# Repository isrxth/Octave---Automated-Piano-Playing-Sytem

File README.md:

###### 🎹 Project Octave

###### 

###### By Team WeBeSyncing

###### 

###### Project Octave is a high-speed, polyphonic, CNC-style robotic piano playing system. Utilizing a multi-microcontroller architecture, ESP-NOW wireless synchronization, and a custom lookahead kinematic engine, Octave translates standard .mid files into precise physical movements, playing an acoustic piano with superhuman speed and accuracy.

https://github.com/user-attachments/assets/f8b78fd2-65e9-428f-8b61-9593326f1c79

###### ✨ Key Features

###### 

###### &#x20;   Polyphonic "Cluster" Engine: Groups simultaneous MIDI notes and calculates a "Center of Gravity" offset, allowing a rigid solenoid block to perfectly strike multiple keys at once.

###### 

###### &#x20;   Anti-Flood Staggering: Automatically spaces out simultaneous polyphonic WebSocket commands by 15ms to prevent Arduino Uno serial buffer overflow and dropped notes.

###### 

###### &#x20;   Lookahead Background Pre-Positioning: The Web UI calculates future moves and silently drives the stepper carriages into position during the natural musical rests, eliminating mechanical latency.

###### 

###### &#x20;   Strict Hardware Interlock: A closed-loop feedback system using ESP-NOW guarantees that solenoids will never fire while the carriage is in transit, completely protecting the 3D-printed mounts from lateral shear forces.

###### 

###### &#x20;   Dynamic Velocity Control: Maps MIDI velocity data to hardware PWM duty cycles, allowing for expressive, dynamic play (Soft vs. Hard strikes), or strict binary toggling.

###### 

###### &#x20;   Asynchronous Web UI: A beautiful, dark-mode TailwindCSS web interface hosted directly on the ESP32. Features live BPM scaling, dynamic clearance tuning, and an interactive virtual keyboard.

###### 

###### &#x20;   Over-The-Air (OTA) Updates: Fully integrated ElegantOTA allows for flashing firmware to the embedded microcontrollers via Wi-Fi without dismantling the piano hardware.

###### 

###### 🧠 System Architecture

###### 

###### Octave uses a distributed computing model to ensure non-blocking, real-time performance.

###### 1\. The Master Node (ESP32)

###### 

###### &#x20;   Hosts the Web UI (test.html) via ESPAsyncWebServer.

###### 

###### &#x20;   Receives WebSocket commands from the user's browser.

###### 

###### &#x20;   Directly drives the Black Key Solenoids (S1 - S5) via hardware PWM.

###### 

###### &#x20;   Broadcasts MOVE commands to the Stepper Node over ESP-NOW.

###### 

###### &#x20;   Sends Serial commands to the Arduino Uno.

###### 

###### 2\. The Stepper Node (ESP32)

###### 

###### &#x20;   Listens for ESP-NOW packets and drives two NEMA 17 stepper motors using AccelStepper.

###### 

###### &#x20;   Motor 1 (White Carriage): Uses sliding-window nearest-neighbor logic to traverse the white keys.

###### 

###### &#x20;   Motor 2 (Black Carriage): Uses inverted, octave-locked kinematics to perfectly align with the irregular 2-and-3 black key clusters.

###### 

###### &#x20;   Reads physical limit switches and transmits AT\_TARGET packets back to the Master to unlock the software thread.

###### 

###### 3\. The Strike Node (Arduino Uno)

###### 

###### &#x20;   Receives ultra-fast Serial packets from the Master ESP32 via a logic level shifter.

###### 

###### &#x20;   Manages a non-blocking 40ms ballistic state machine for the 7 White Key Solenoids.

###### 

###### &#x20;   Utilizes a custom 1kHz Software PWM engine for digital pins to maintain a 23% low-current hold state, preventing coil burnout.

###### 

###### 🛠️ Hardware Requirements

###### 

###### &#x20;   2x ESP32 Development Boards

###### 

###### &#x20;   1x Arduino Uno R3

###### 

###### &#x20;   2x NEMA 17 Stepper Motors (w/ TMC2209 or A4988 Drivers)

###### 

###### &#x20;   12x 15N Push-Pull Solenoids

###### 

###### &#x20;   3D-Printed Carriages \& Solenoid Mounts

###### 

###### &#x20;   12V / 24V Power Supplies \& Logic Level Converters (HW-209)

###### 

###### 🛜 Changing the Wi-Fi Network Name (SSID)

###### 

###### By default, the Master ESP32 creates a hotspot named POCOF3. Because the Master and Stepper nodes must communicate, their network credentials must match perfectly.

###### 

###### &#x20;   Open solenoid\_esp.cpp (Master) and modify:

###### &#x20;   C++

###### 

###### &#x20;   const char\* hotspotSSID     = "Project\_Octave"; // Your new name

###### &#x20;   const char\* hotspotPassword = "00000000";       // Your new password

###### 

###### &#x20;   Open stepper\_esp.cpp (Stepper) and ensure lines 8 \& 9 match exactly.

###### 

###### &#x20;   Re-flash both ESP32s.

###### 

###### 🚀 Installation \& Setup

###### 1\. Flash the Firmware

###### 

###### &#x20;   Open the project in PlatformIO or the Arduino IDE.

###### 

###### &#x20;   Install the required libraries: ESPAsyncWebServer, AsyncTCP, AccelStepper, ElegantOTA.

###### 

###### &#x20;   Flash solenoid\_esp.cpp and stepper\_esp.cpp to your respective ESP32s.

###### 

###### &#x20;   Flash solenoid\_uno.ino to your Arduino Uno.

###### 

###### 2\. Connect to the UI

###### 

###### &#x20;   Power on the Master ESP32.

###### 

###### &#x20;   Connect your computer/tablet to the Octave Wi-Fi hotspot.

###### 

###### &#x20;   Open your web browser and navigate to the ESP32's IP address (default: http://192.168.4.1).

###### 

###### &#x20;   Enter the IP into the Master Control UI and click CONNECT WS.

###### 

###### 🎹 Polyphony Limits \& Hardware Constraints

###### 

###### While the software fully supports polyphonic MIDI playback, it is bound by the physical laws of the rigid 3D-printed solenoid blocks.

###### 

###### &#x20;   The Span Limit: The system can play multiple notes at the exact same time, but they must physically fit under the 7-solenoid white carriage or the 5-solenoid black carriage. \* The Outlier Drop: If a MIDI file demands a C3 and a C5 simultaneously, the carriage cannot stretch. The software's Cluster Engine will calculate a "Center of Gravity" to cover the densest cluster of notes and safely ignore the unreachable outliers to prevent the motors from destroying the mounts.

###### 

###### 🎯 Usage \& Tuning

###### 

###### Once connected to the UI, you can calibrate Octave to match your specific physical build:

###### 

###### &#x20;   White Home / Black Home: Adjust these steps to perfectly align the 3D-printed carriages over the physical C3 octave. (Note: Black Home uses inverted kinematics, so its home step is a high value like 2400).

###### 

###### &#x20;   Clearance (ms): The mechanical time allowed for the 15N solenoid springs to pull the metal slugs out of the keybed before the stepper motors are allowed to move. Lower this value for faster songs, but ensure the slugs clear the keys to avoid lateral dragging.

###### 

###### &#x20;   Target BPM: The live tempo scaler. You can speed up or slow down a loaded MIDI file in real-time.

###### 

###### 📝 License \& Credits

## Schematics & PCB

###### 

###### Developed by Team WeBeSyncing.

###### Built for the intersection of Embedded Systems, Mechanical Engineering, and Music.

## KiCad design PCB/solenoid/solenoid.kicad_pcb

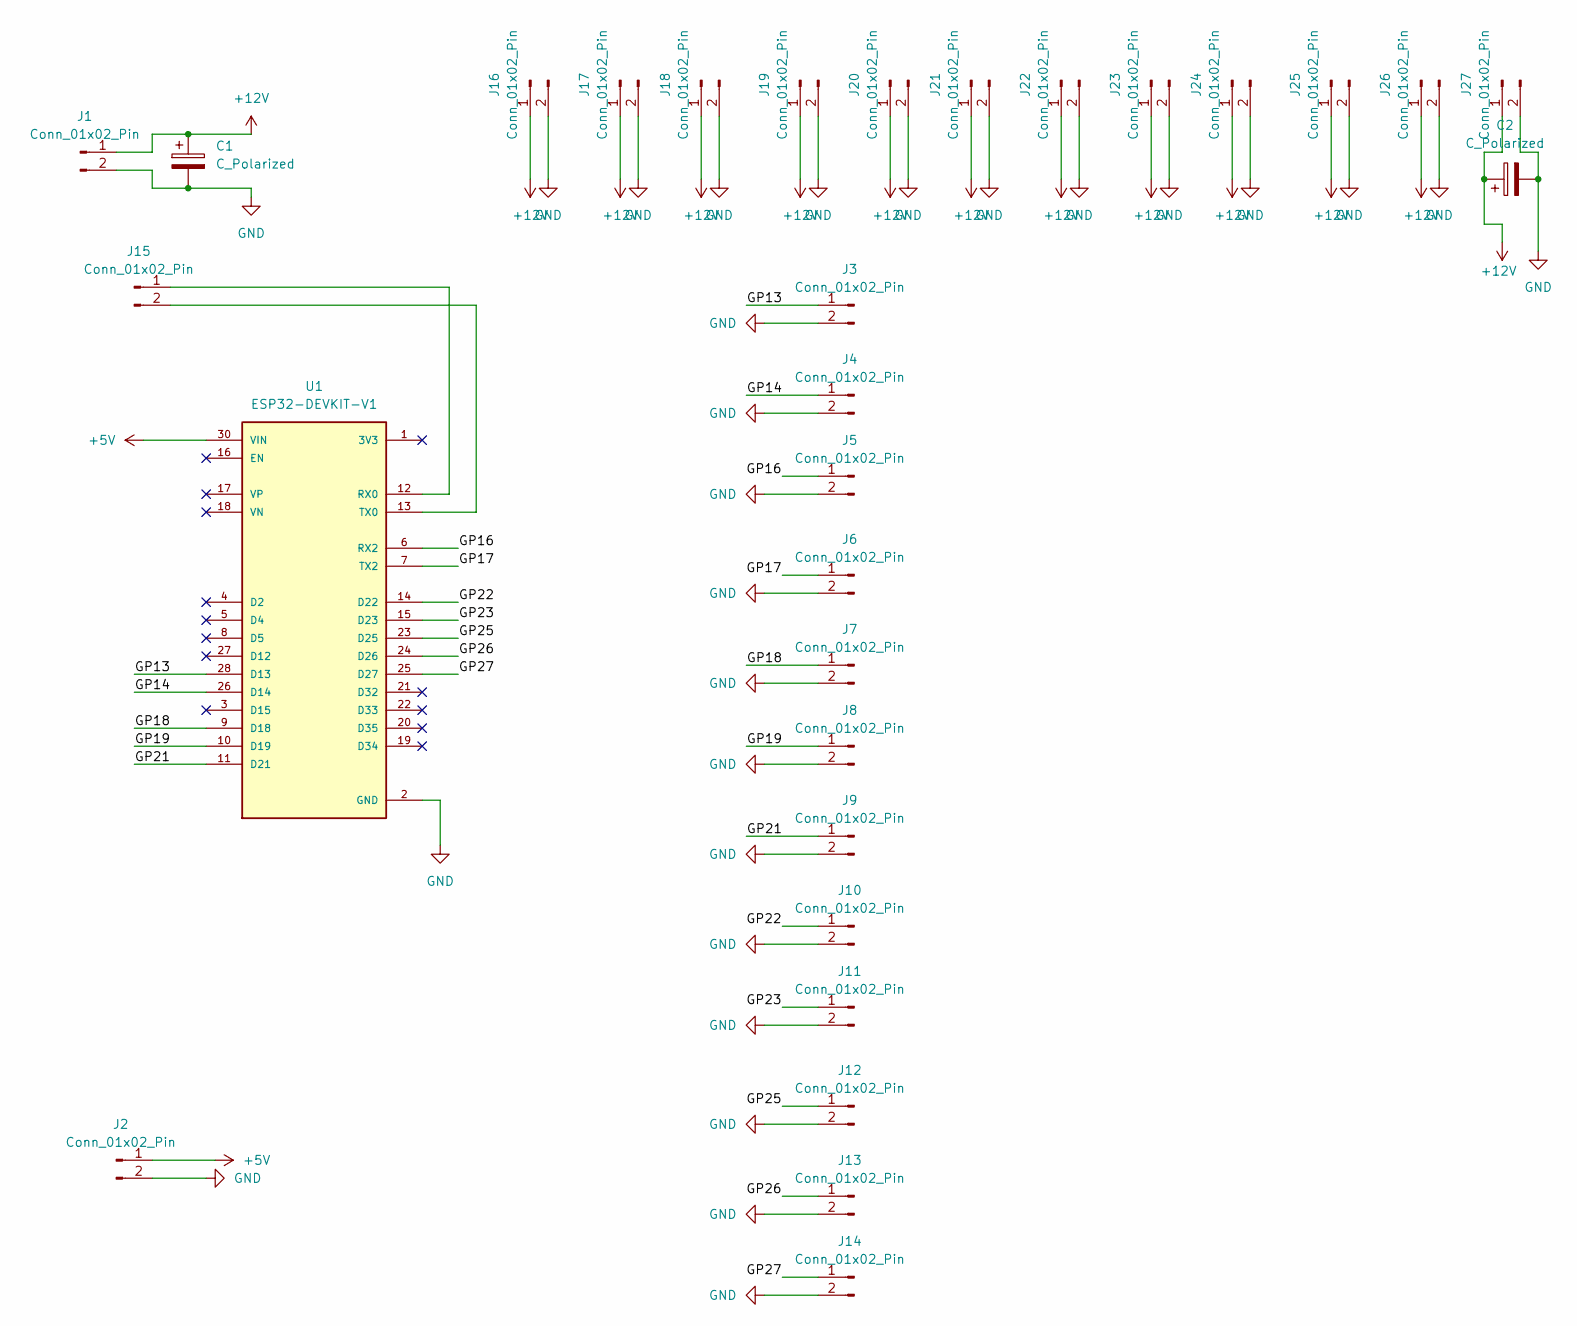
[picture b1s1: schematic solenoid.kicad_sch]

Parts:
C1, C2: C_Polarized; CP_Radial_D10.0mm_P5.00mm
J1, J2, J16, J17, J18, J19, J20, J21, J22, J23, J24, J25, J26, J27: Conn_01x02_Pin; TerminalBlock_Phoenix_PT-1,5-2-3.5-H_1x02_P3.50mm_Horizontal
J3, J4, J5, J6, J7, J8, J9, J10, J11, J12, J13, J14, J15: Conn_01x02_Pin; PinHeader_1x02_P2.54mm_Vertical
U1: ESP32-DEVKIT-V1; MODULE_ESP32_DEVKIT_V1; PARTREV N/A

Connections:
+5V: J2.1, U1.30 (VIN)
+12V: C1.1, C2.1, J1.1, J16.1, J17.1, J18.1, J19.1, J20.1, J21.1, J22.1, J23.1, J24.1, J25.1, J26.1, J27.1
/GP13: J3.1, U1.28 (D13)
/GP14: J4.1, U1.26 (D14)
/GP16: J5.1, U1.6 (RX2)
/GP17: J6.1, U1.7 (TX2)
/GP18: J7.1, U1.9 (D18)
/GP19: J8.1, U1.10 (D19)
/GP21: J9.1, U1.11 (D21)
/GP22: J10.1, U1.14 (D22)
/GP23: J11.1, U1.15 (D23)
/GP25: J12.1, U1.23 (D25)
/GP26: J13.1, U1.24 (D26)
/GP27: J14.1, U1.25 (D27)
GND: C1.2, C2.2, J1.2, J2.2, J3.2, J4.2, J5.2, J6.2, J7.2, J8.2, J9.2, J10.2, J11.2, J12.2, J13.2, J14.2, J16.2, J17.2, J18.2, J19.2, J20.2, J21.2, J22.2, J23.2, J24.2, J25.2, J26.2, J27.2, U1.2 (GND), U1.29 (GND)
unnamed: J15.1, U1.12 (RX0)
unnamed: J15.2, U1.13 (TX0)

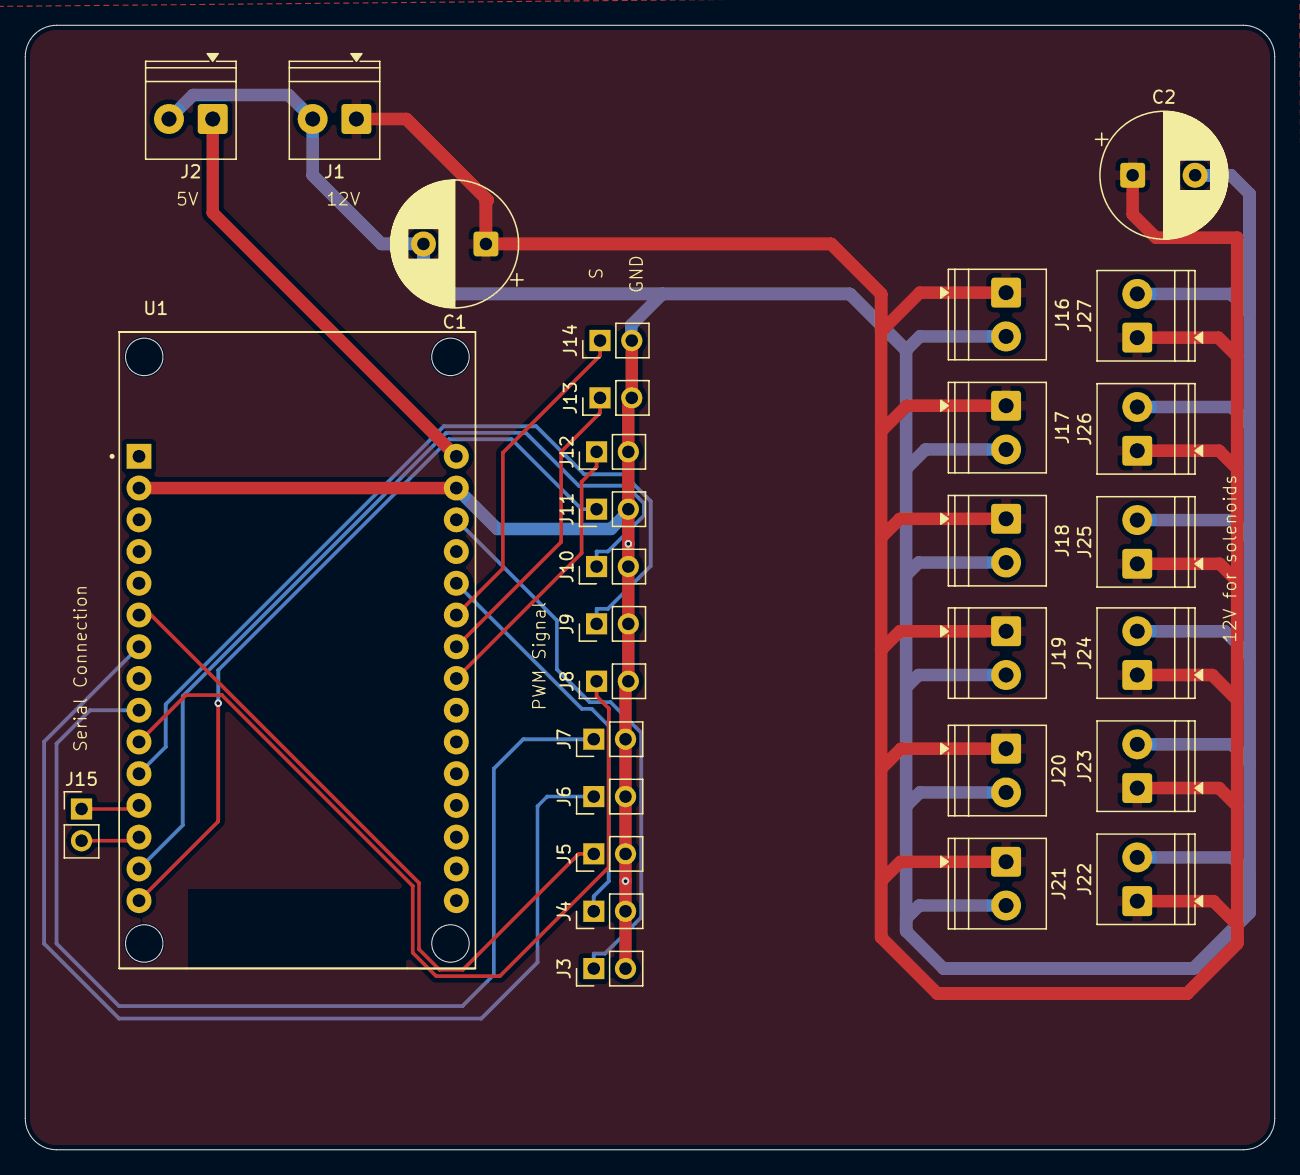
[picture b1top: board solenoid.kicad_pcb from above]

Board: 2 copper layers, 100.0 x 90.0 mm, 30 parts (0 on the bottom side), 17 nets.

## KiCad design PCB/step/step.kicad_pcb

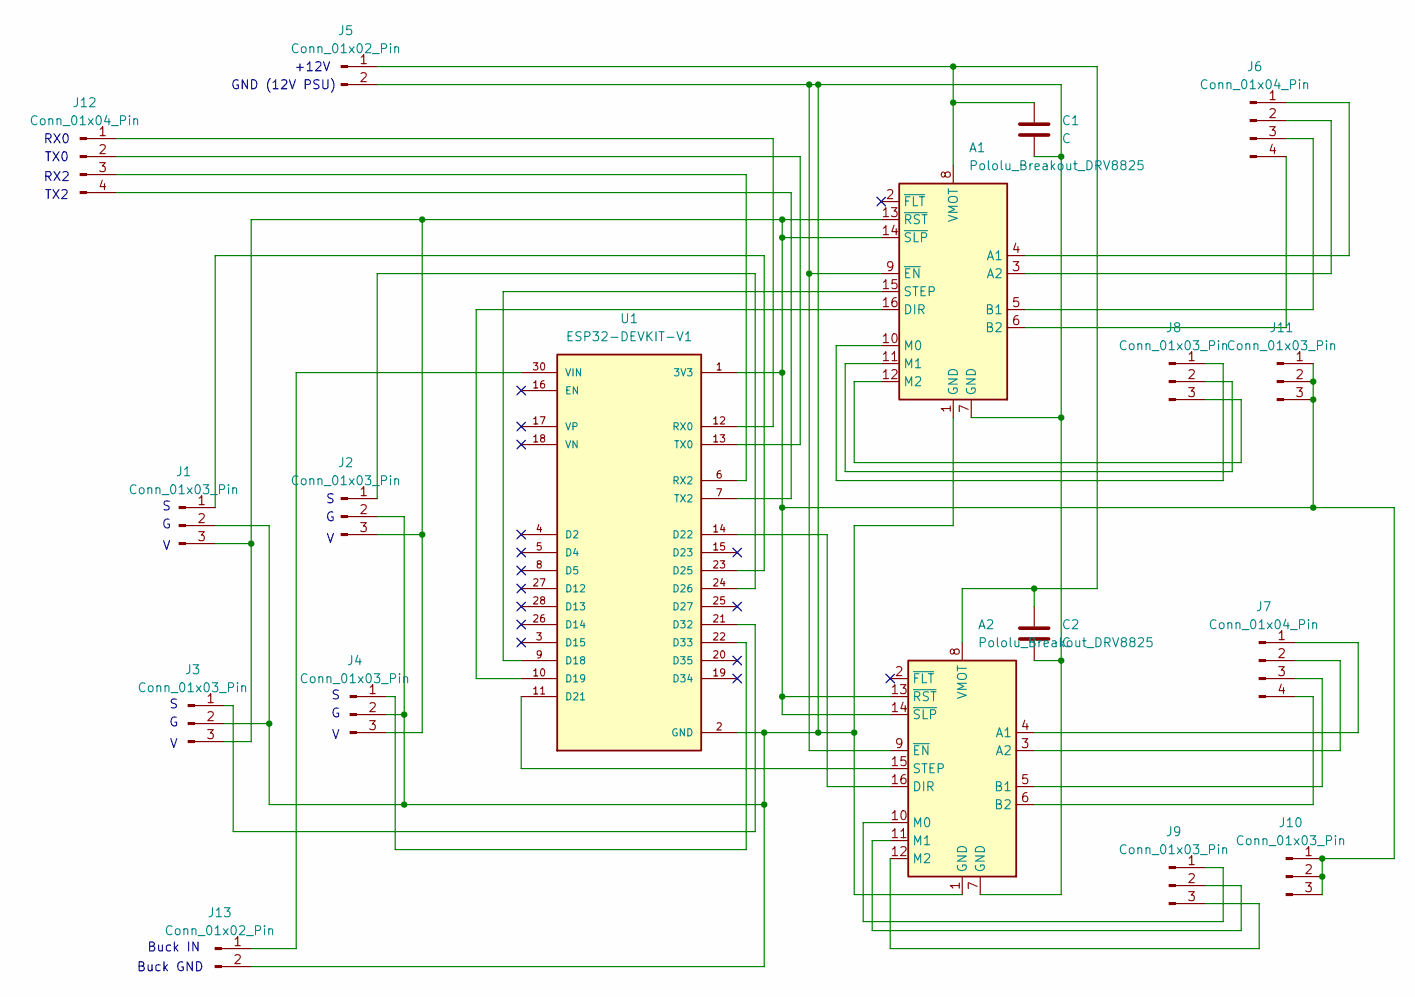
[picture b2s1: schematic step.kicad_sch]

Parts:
A1, A2: Pololu_Breakout_DRV8825; Pololu_Breakout-16_15.2x20.3mm
C1, C2: C; CP_Radial_D8.0mm_P3.50mm
J1, J2, J3, J4, J8, J9, J10, J11: Conn_01x03_Pin; PinHeader_1x03_P2.54mm_Vertical
J5, J13: Conn_01x02_Pin; TerminalBlock_Phoenix_PT-1,5-2-3.5-H_1x02_P3.50mm_Horizontal
J6, J7, J12: Conn_01x04_Pin; PinHeader_1x04_P2.54mm_Vertical
U1: ESP32-DEVKIT-V1; MODULE_ESP32_DEVKIT_V1; PARTREV N/A

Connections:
GND: A1.1 (GND), A1.7 (GND), A1.9 (~EN), A2.1 (GND), A2.7 (GND), A2.9 (~EN), C1.2, C2.2, J1.2, J2.2, J3.2, J4.2, J5.2, J13.2, U1.2 (GND), U1.29 (GND)
unnamed: A1.4 (A1), J6.1
unnamed: A1.3 (A2), J6.2
unnamed: A1.5 (B1), J6.3
unnamed: A1.6 (B2), J6.4
unnamed: A1.16 (DIR), U1.10 (D19)
unnamed: A1.10 (M0), J8.1
unnamed: A1.11 (M1), J8.2
unnamed: A1.12 (M2), J8.3
unnamed: A1.15 (STEP), U1.9 (D18)
unnamed: A1.8 (VMOT), A2.8 (VMOT), C1.1, C2.1, J5.1
unnamed: A1.13 (~RST), A1.14 (~SLP), A2.13 (~RST), A2.14 (~SLP), J1.3, J2.3, J3.3, J4.3, J10.1, J10.2, J10.3, J11.1, J11.2, J11.3, U1.1 (3V3)
unnamed: A2.4 (A1), J7.1
unnamed: A2.3 (A2), J7.2
unnamed: A2.5 (B1), J7.3
unnamed: A2.6 (B2), J7.4
unnamed: A2.16 (DIR), U1.14 (D22)
unnamed: A2.10 (M0), J9.1
unnamed: A2.11 (M1), J9.2
unnamed: A2.12 (M2), J9.3
unnamed: A2.15 (STEP), U1.11 (D21)
unnamed: J1.1, U1.23 (D25)
unnamed: J2.1, U1.24 (D26)
unnamed: J3.1, U1.21 (D32)
unnamed: J4.1, U1.22 (D33)
unnamed: J12.1, U1.12 (RX0)
unnamed: J12.2, U1.13 (TX0)
unnamed: J12.3, U1.6 (RX2)
unnamed: J12.4, U1.7 (TX2)
unnamed: J13.1, U1.30 (VIN)

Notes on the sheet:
RX2
Buck GND
Buck IN
TX2
RX0
GND (12V PSU)
+12V
TX0

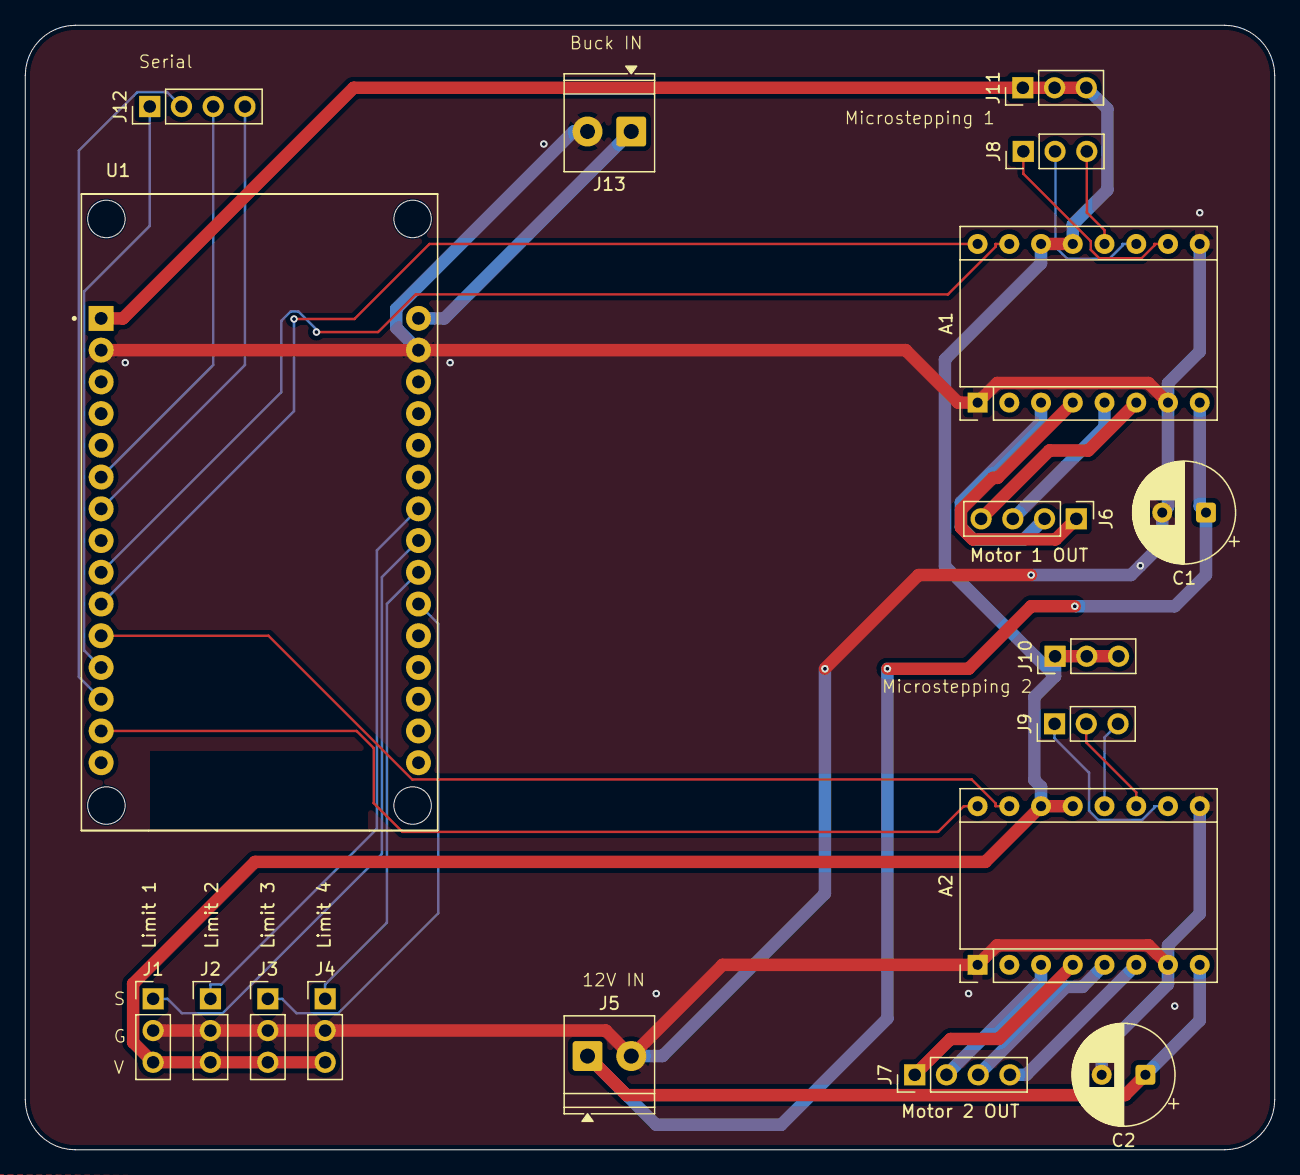
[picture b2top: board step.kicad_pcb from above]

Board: 2 copper layers, 100.0 x 90.0 mm, 18 parts (0 on the bottom side), 30 nets.

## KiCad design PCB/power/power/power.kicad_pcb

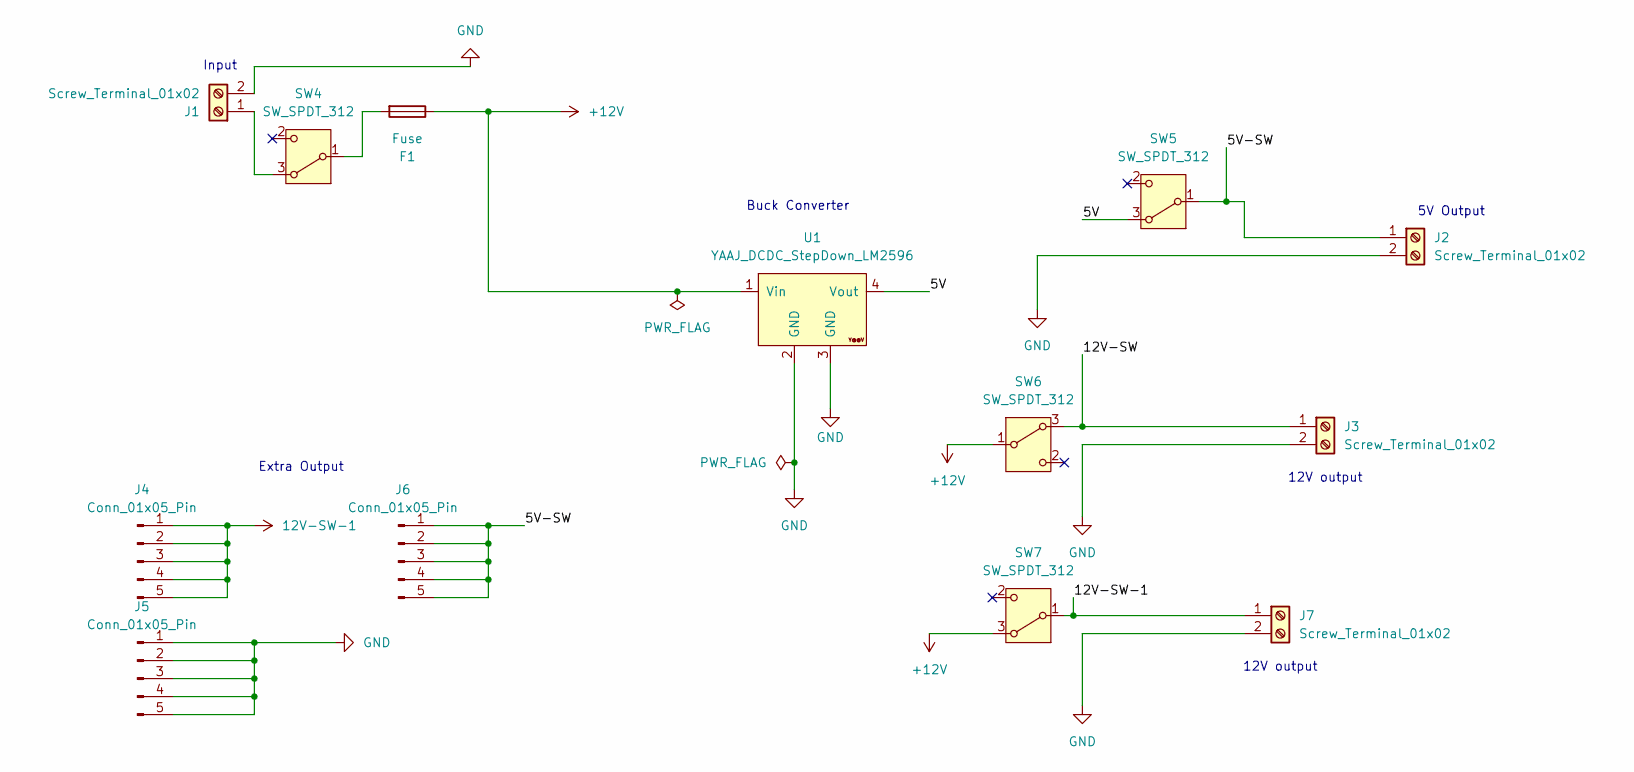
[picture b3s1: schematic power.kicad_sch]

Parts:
F1: Fuse; Fuseholder_Clip-5x20mm_Bel_FC-203-22_Lateral_P17.80x5.00mm_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
J1, J2, J3, J7: Screw_Terminal_01x02; TerminalBlock_MetzConnect_Type101_RT01602HBWC_1x02_P5.08mm_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
J4, J5, J6: Conn_01x05_Pin; PinSocket_1x05_P2.54mm_Vertical
SW4, SW5, SW6, SW7: SW_SPDT_312; PinHeader_1x03_P2.54mm_Vertical
U1: YAAJ_DCDC_StepDown_LM2596

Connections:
12V-SW-1: J4.1, J4.2, J4.3, J4.4, J4.5, J7.1, SW7.1 (B)
+12V: F1.1, SW6.1 (B), SW7.3 (A), U1.1 (Vin)
/5V: SW5.3 (A), U1.4 (Vout)
/5V-SW: J2.1, J6.1, J6.2, J6.3, J6.4, J6.5, SW5.1 (B)
/12V-SW: J3.1, SW6.3 (A)
GND: J1.2, J2.2, J3.2, J5.1, J5.2, J5.3, J5.4, J5.5, J7.2, U1.2 (GND), U1.3 (GND)
unnamed: J1.1, SW4.3 (A)
unnamed: F1.2, SW4.1 (B)

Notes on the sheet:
12V output
Buck Converter
5V Output
Extra Output
Input

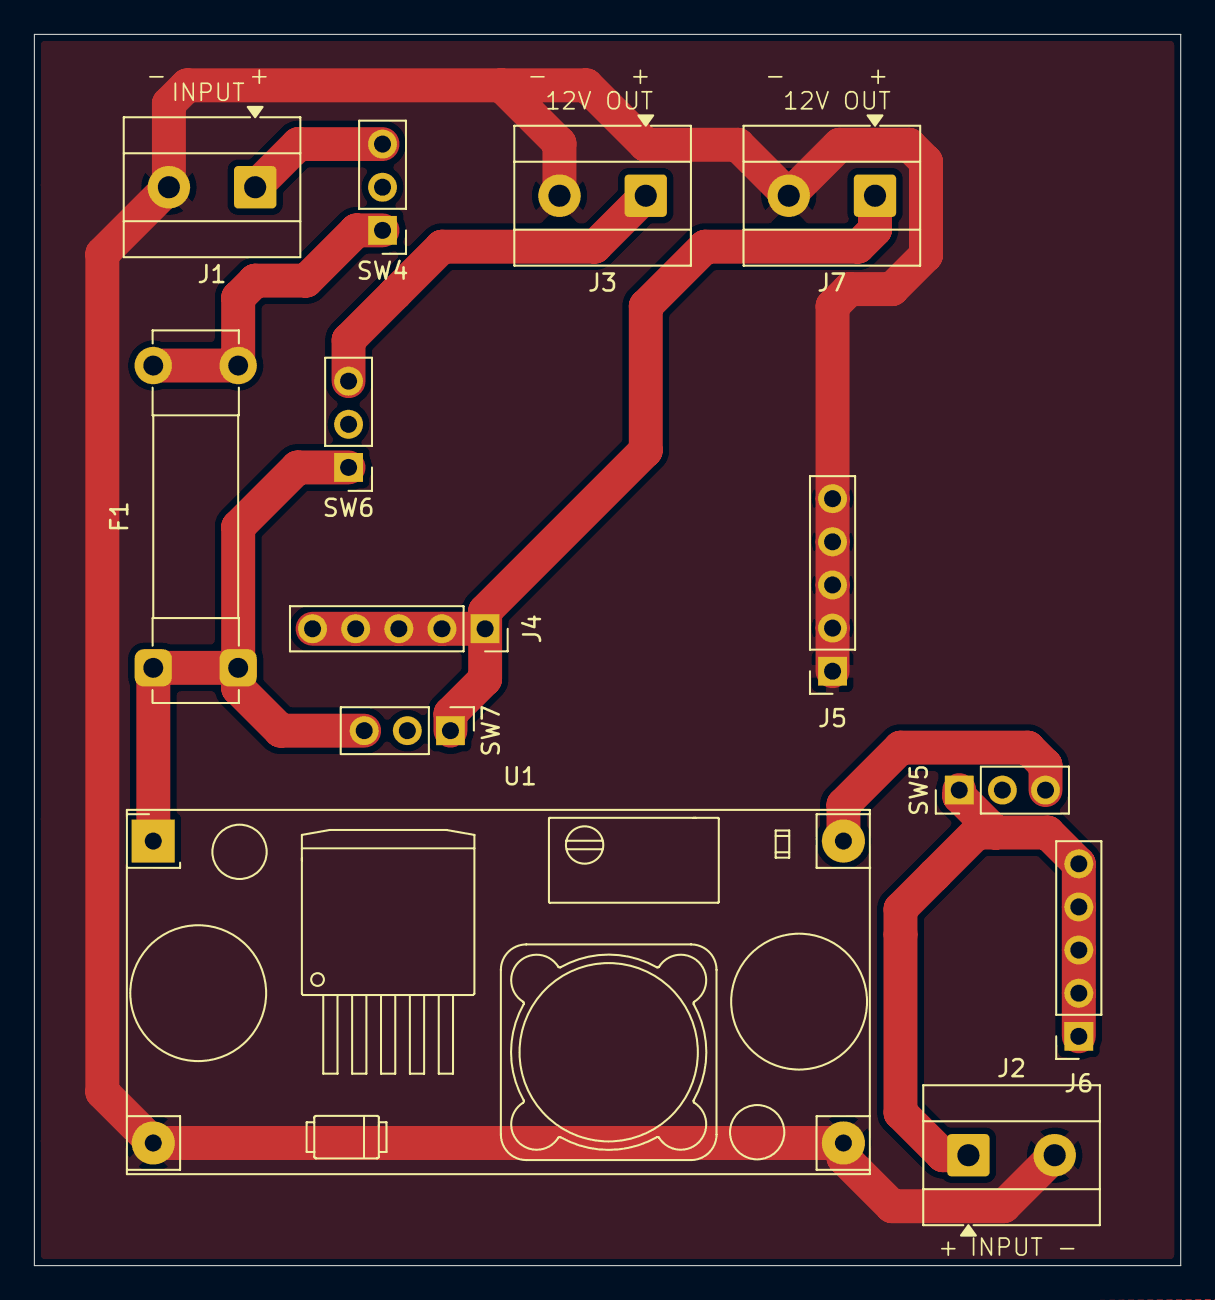
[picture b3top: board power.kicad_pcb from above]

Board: 2 copper layers, 67.5 x 72.5 mm, 13 parts (0 on the bottom side), 8 nets.

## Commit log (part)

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2026-06-30 Working Version of Code
2026-06-30 README Update
2026-06-30 README Update 2
